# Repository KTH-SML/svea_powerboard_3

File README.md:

# Svea Powerboard Rev3

Repository structure:

- `firmware/` — Zephyr firmware workspace (intended root for app/boards/modules as this grows).
- `hardware/kicad/` — KiCad project root, symbols, footprints, models, datasheets, and manufacturing assets.
	- `hardware/kicad/*.kicad_sch` — all schematic sheets are flattened in the project root for simpler external-tool dependency resolution.
- `scripts/` — migration/cleanup/utility scripts and helper tooling.

Can be viewed on [Kicad viewer](https://kicanvas.org/?repo=https%3A%2F%2Fgithub.com%2FKTH-SML%2Fsvea_powerboard_3%2Ftree%2Fmain%2Fhardware%2Fkicad)
## Working folders

- Open KiCad project from `hardware/kicad/svea_powerboard_rev3.kicad_pro`.
- Run helper scripts from repo root, for example: `python scripts/rebuild_parent_hierarchy.py`.

## Notes

- Keep all generated/temporary KiCad artifacts out of version control via `.gitignore`.
- Keep firmware and hardware changes in separate commits when possible.

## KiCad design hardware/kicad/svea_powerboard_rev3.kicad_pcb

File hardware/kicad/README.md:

# I2C Rail Audit (`SCL_SLOW` / `SDA_SLOW`)

Generated on `2026-03-05` from:
- Schematic: `hardware/kicad/svea_powerboard_rev3.kicad_sch`
- Fresh netlist: `build/kicad/quality/netlist_i2c_audit.xml`

All addresses below are **7-bit I2C addresses unless explicitly noted otherwise**.

## Scope and method
1. Exported a fresh netlist with `kicad-cli sch export netlist`.
2. Enumerated every node on `SCL_SLOW` and `SDA_SLOW`.
3. Derived addresses from **actual pin straps + datasheet address tables**.
4. Did not trust symbol comments/labels as source of truth.

## Rail summary
| Rail | Pull-up | Net notes |
|---|---|---|
| `SCL_SLOW` | `R105 = 2.2k` to `+3V3` | Connected to all on-bus devices, `U83` connector pin 10, and `JP2001` pin 1 |
| `SDA_SLOW` | `R118 = 2.2k` to `+3V3` | Connected to all on-bus devices, `U83` connector pin 12, and `JP2002` pin 1 |

## I2C device matrix (address + speed)
| Ref | Device | Bus state on this board | Address (7-bit) | Supported I2C frequency (datasheet) | Strap / decode evidence |
|---|---|---|---|---|---|
| `CUR_1` | `INA3221AIRGVR` | Active on `SCL_SLOW/SDA_SLOW` | `0x40` | Fast + HS: up to `2.44 MHz` | `A0` via `R98` to `GND`; INA3221 address table (`A0=GND`) |
| `CUR_2` | `INA3221AIRGVR` | Active on `SCL_SLOW/SDA_SLOW` | `0x41` | Fast + HS: up to `2.44 MHz` | `A0` via `R162` to `+3V3`; INA3221 address table (`A0=VS`) |
| `U304` | `PCAL6524HEAZ` | Active on `SCL_SLOW/SDA_SLOW` | `0x23` | Fm+: up to `1 MHz` | `ADDR` via `R19` to `+3V3`; datasheet Table 4 gives `0x46/0x47` (8-bit) |
| `U3404` | `PCAL6524HEAZ` | Active on `SCL_SLOW/SDA_SLOW` | `0x22` | Fm+: up to `1 MHz` | `ADDR` via `R243` to `GND`; datasheet Table 4 gives `0x44/0x45` (8-bit) |
| `U44` | `MCP4725A0T-E/CH` | Active on `SCL_SLOW/SDA_SLOW` | `0x60` | Standard/Fast/HS: up to `3.4 MHz` | `A0` pin to `GND`; `A2/A1=00` option for A0 variant |
| `U601` | `TPL0401B-10DCKR` | Active on `SCL_SLOW/SDA_SLOW` | `0x3E` | Standard/Fast: up to `400 kHz` | TPL0401B bit address table (`0111110b`) |
| `U72` | `INA226AIDGSR` | Active on `SCL_SLOW/SDA_SLOW` | `0x4E` | Fast + HS: up to `2.94 MHz` | `A1=SCL`, `A0=SDA` |
| `U78` | `PCA9685PW,118` | Active on `SCL_SLOW/SDA_SLOW` | `0x61` | Fm+: up to `1 MHz` | `A5=1`, `A0=1` via `R186`, `A4..A1=0` via `R184,R183,R182,R181` |
| `U80` | `BQ7694202PFBR` | Active on `SCL_SLOW/SDA_SLOW` | `0x08` (default) | `100/400 kHz` | Datasheet default I2C target bytes `0x10/0x11` (8-bit) |
| `U81` | `INA226AIDGSR` | Active on `SCL_SLOW/SDA_SLOW` | `0x4F` | Fast + HS: up to `2.94 MHz` | `A1=SCL`, `A0=SCL` |
| `U1` | `LSM6DSOXTR` | Active on `SCL_SLOW/SDA_SLOW` | `0x6B` | Standard/Fast: up to `400 kHz` | `SA0` tied high (`SDO/SA0=+3V3`) |
| `U104` | `ADS1115IRUGT` | Active on `SCL_SLOW/SDA_SLOW` | `0x49` | Standard/Fast/HS: up to `3.4 MHz` | `ADDR=+3V3` |
| `U65` | `HUSB238A-BB001-QN16R` | **Isolated by default** (`JP2001`,`JP2002` open) | Conditional: datasheet notation is `62H` (`ADDR=VDD`) or `42H` (`ADDR=GND`); if those are 8-bit transfer bytes, equivalent 7-bit addresses are `0x31` / `0x21`; floating `ADDR` => GPIO mode (no I2C address) | Fast mode: up to `400 kHz` | `ADDR/ORIENT` is not hard-strapped to VDD/GND in this design: `U65.ADDR` -> `R2007` -> `USB-C/I2C/EN` -> `U302` -> `U304` |

`U83` is a direct bus connector endpoint (`SCL_SLOW/SDA_SLOW`) and can add external I2C devices/addresses.

## Findings that matter before ordering
1. No on-board 7-bit address collisions were found on `SCL_SLOW/SDA_SLOW` in this revision.
2. **PCAL6524 address format trap:** datasheet table is shown in 8-bit transfer form (`0x44/0x45`, `0x46/0x47`). Typical firmware APIs want 7-bit (`0x22`, `0x23`).
3. `U83` exposes the same rail externally, so any plugged module can still create address conflicts.
4. `U65` only has a valid I2C address if `ADDR/ORIENT` is forced high or low during initialization; if it is floating at init, the part enters GPIO mode.

## Same-bus compatibility check
1. **Clock-rate compatibility:** all active devices are compatible at `<= 400 kHz`; do not run this shared bus above `400 kHz` because `U601`, `U1`, and `U80` top out at fast/400 kHz.
2. **Mixed fast/HS parts are fine** as long as the controller keeps the bus at the common safe rate (`100 kHz` or `400 kHz`).
3. **Protocol behavior to account for in firmware:**
   - `U78` (`PCA9685`) has default All-Call behavior (address group behavior exists in addition to its normal target address).
   - `U104` (`ADS1115`) supports SMBus/general-call features.
   - `CUR_1/CUR_2/U72/U81` (`INA3221`/`INA226`) include SMBus-style timeout behavior.
   - `U80` (`BQ76942`) can require/expect settings such as speed/CRC mode depending on configuration.
4. **Pull-up / loading margin:** bus pull-ups are `2.2k` to `3.3V` (`~1.5 mA` sink current when line is LOW). This is generally fine for on-board population, but external modules on `U83` may add parallel pull-ups and increase sink-current/rise-time stress.
5. **If enabling `U65` onto this bus:** it is still frequency-compatible (`400 kHz` fast mode), but ensure `ADDR/ORIENT` is deterministically forced HIGH or LOW at init; floating means GPIO mode and no valid I2C target address.

## Recommended pre-order checks
1. Keep firmware-side addresses in 7-bit form (especially `PCAL6524` and `BQ76942`, where many docs show 8-bit transfer bytes).
2. If you plan to use the `U83` external connector, reserve/document external module addresses before assembly.

## Datasheet references used
All datasheets used for this audit are in `hardware/kicad/datasheets/`:
- `INA3221AIRGVR_TI.pdf`
- `INA226AIDGSR_TI.pdf`
- `ADS1115IDGST_TI.pdf`
- `PCAL6524DS_NXP.pdf`
- `PCA9685PW_118_NXP.pdf`
- `TPL0401B-10-Q1_TI.pdf`
- `BQ7694202PFBR_TI.pdf`
- `LSM6DSOX_C481766.pdf`
- `MCP4725A0T-E-CH_MICROCHIP.pdf`
- `HUSB238A-BB001-QN16R.pdf` (checked for the optional jumper-isolated path)

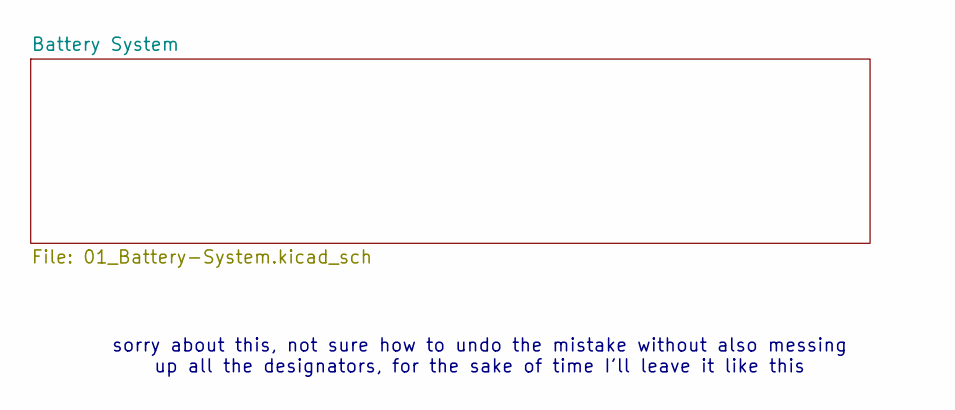
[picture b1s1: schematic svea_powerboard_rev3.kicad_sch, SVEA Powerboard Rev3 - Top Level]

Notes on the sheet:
sorry about this, not sure how to undo the mistake without also messing up all the designators, for the sake of time I'll leave it like this

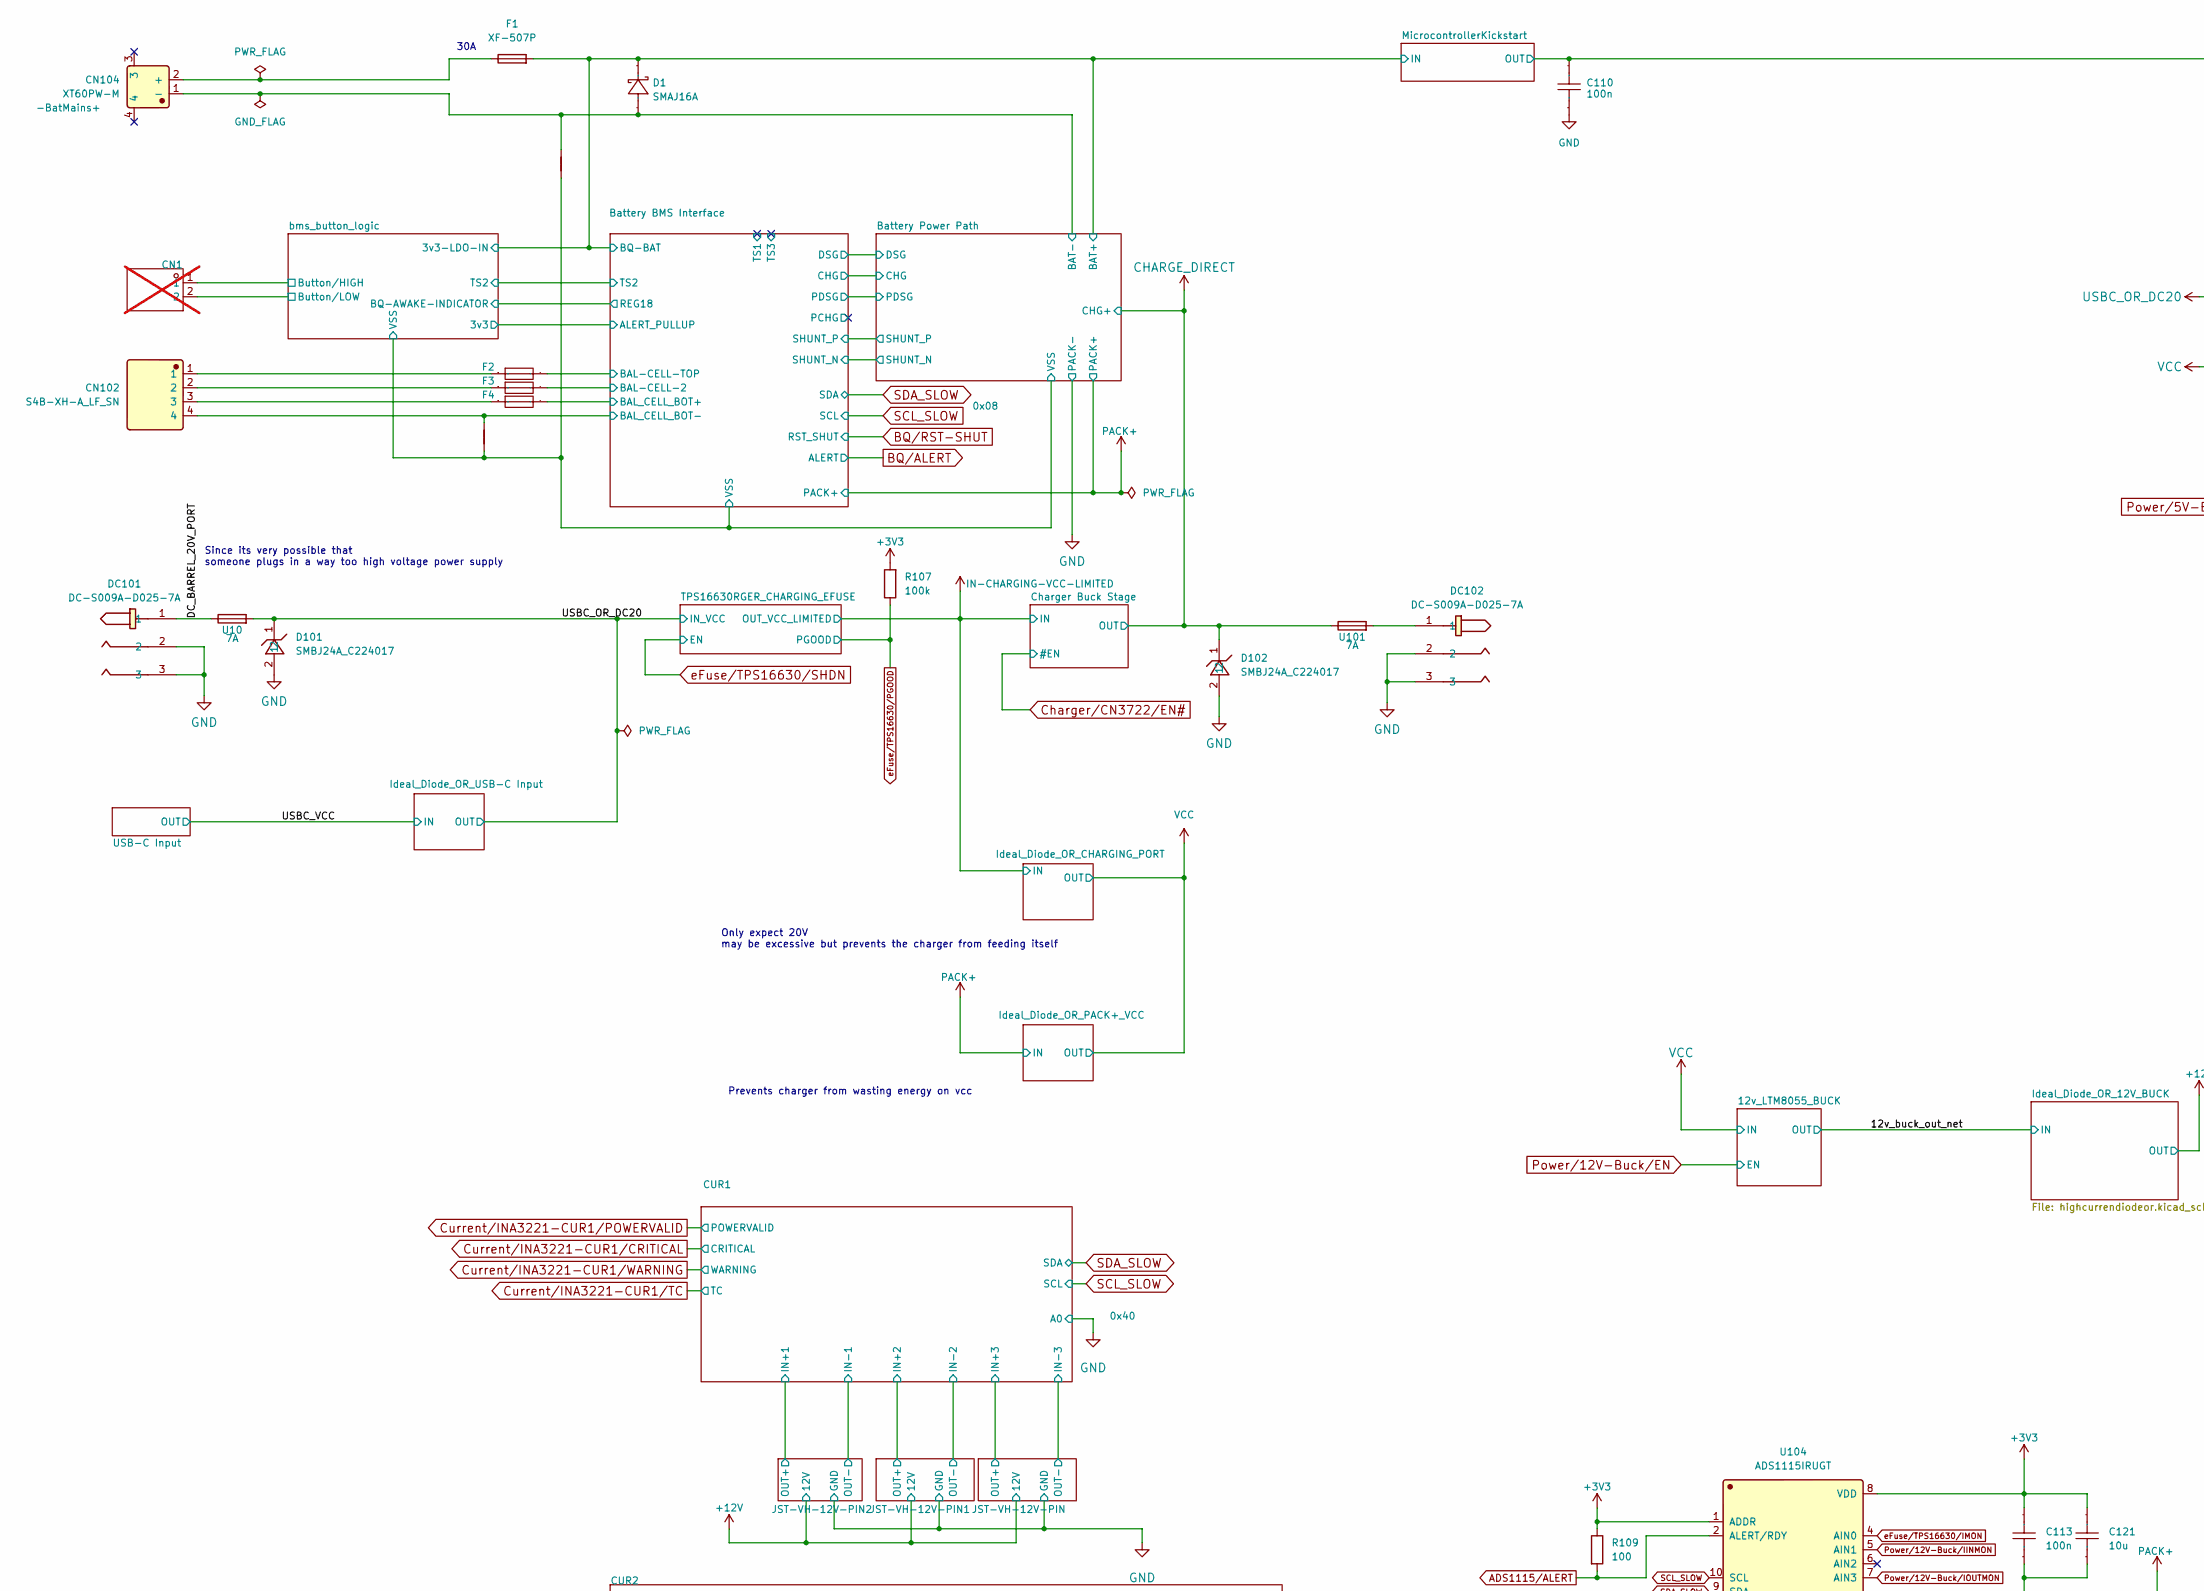
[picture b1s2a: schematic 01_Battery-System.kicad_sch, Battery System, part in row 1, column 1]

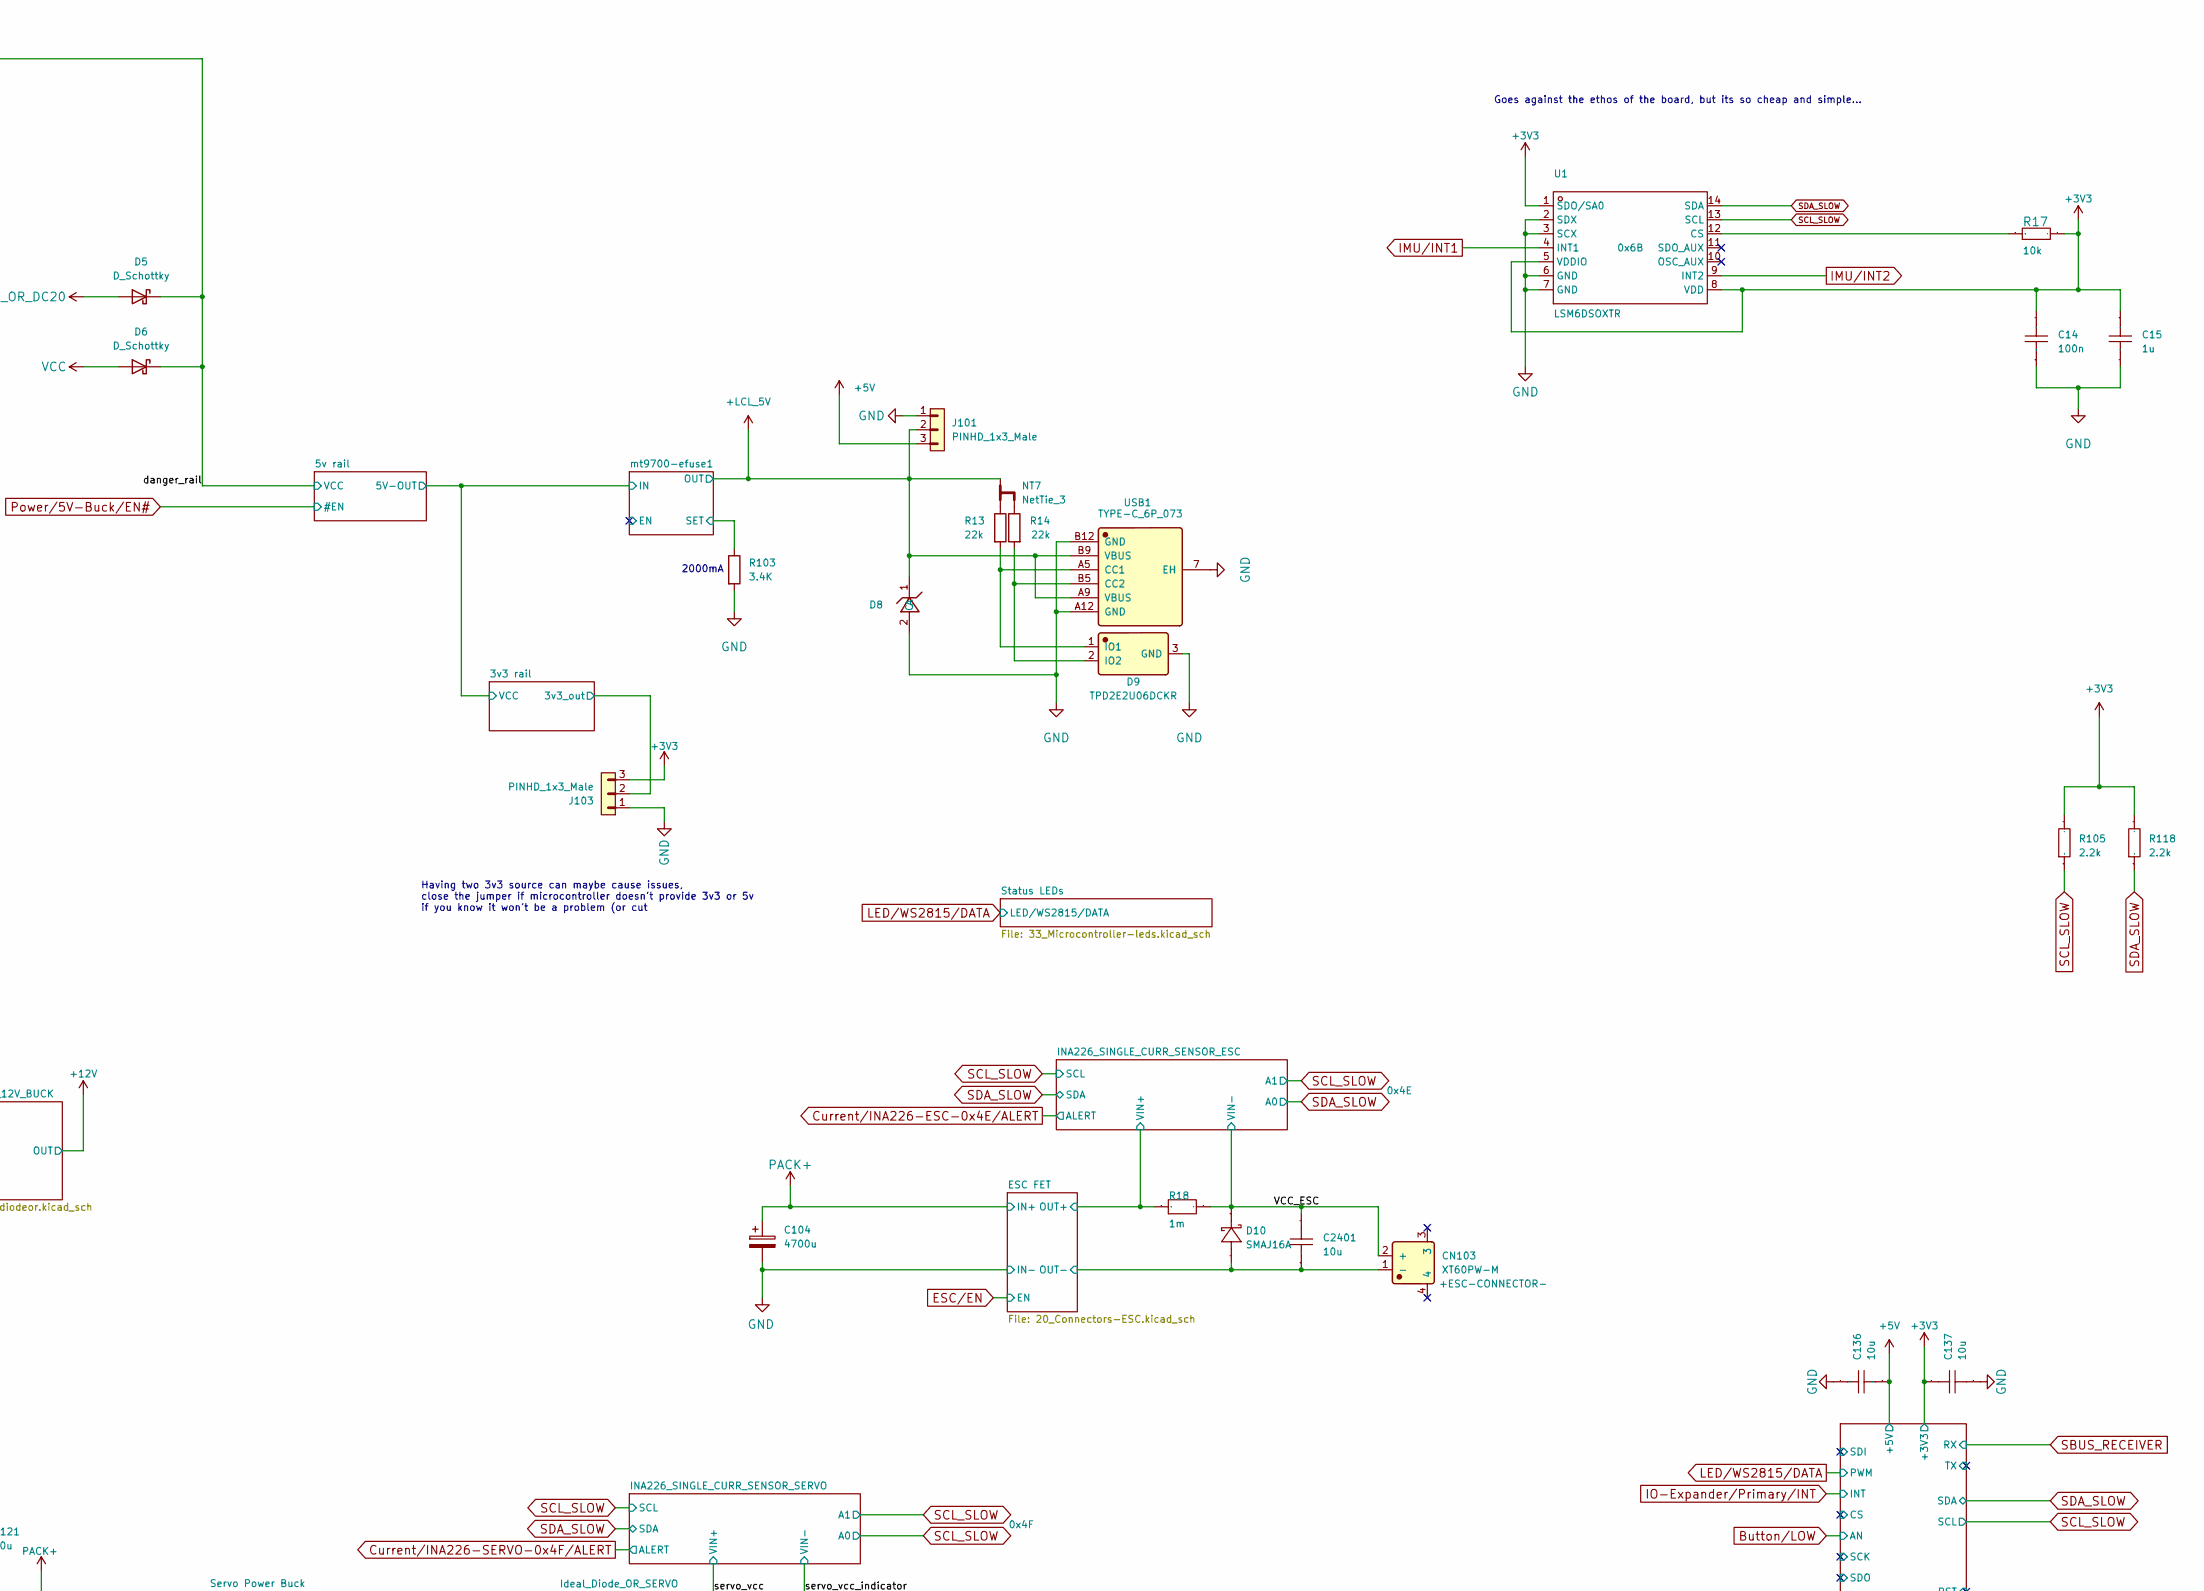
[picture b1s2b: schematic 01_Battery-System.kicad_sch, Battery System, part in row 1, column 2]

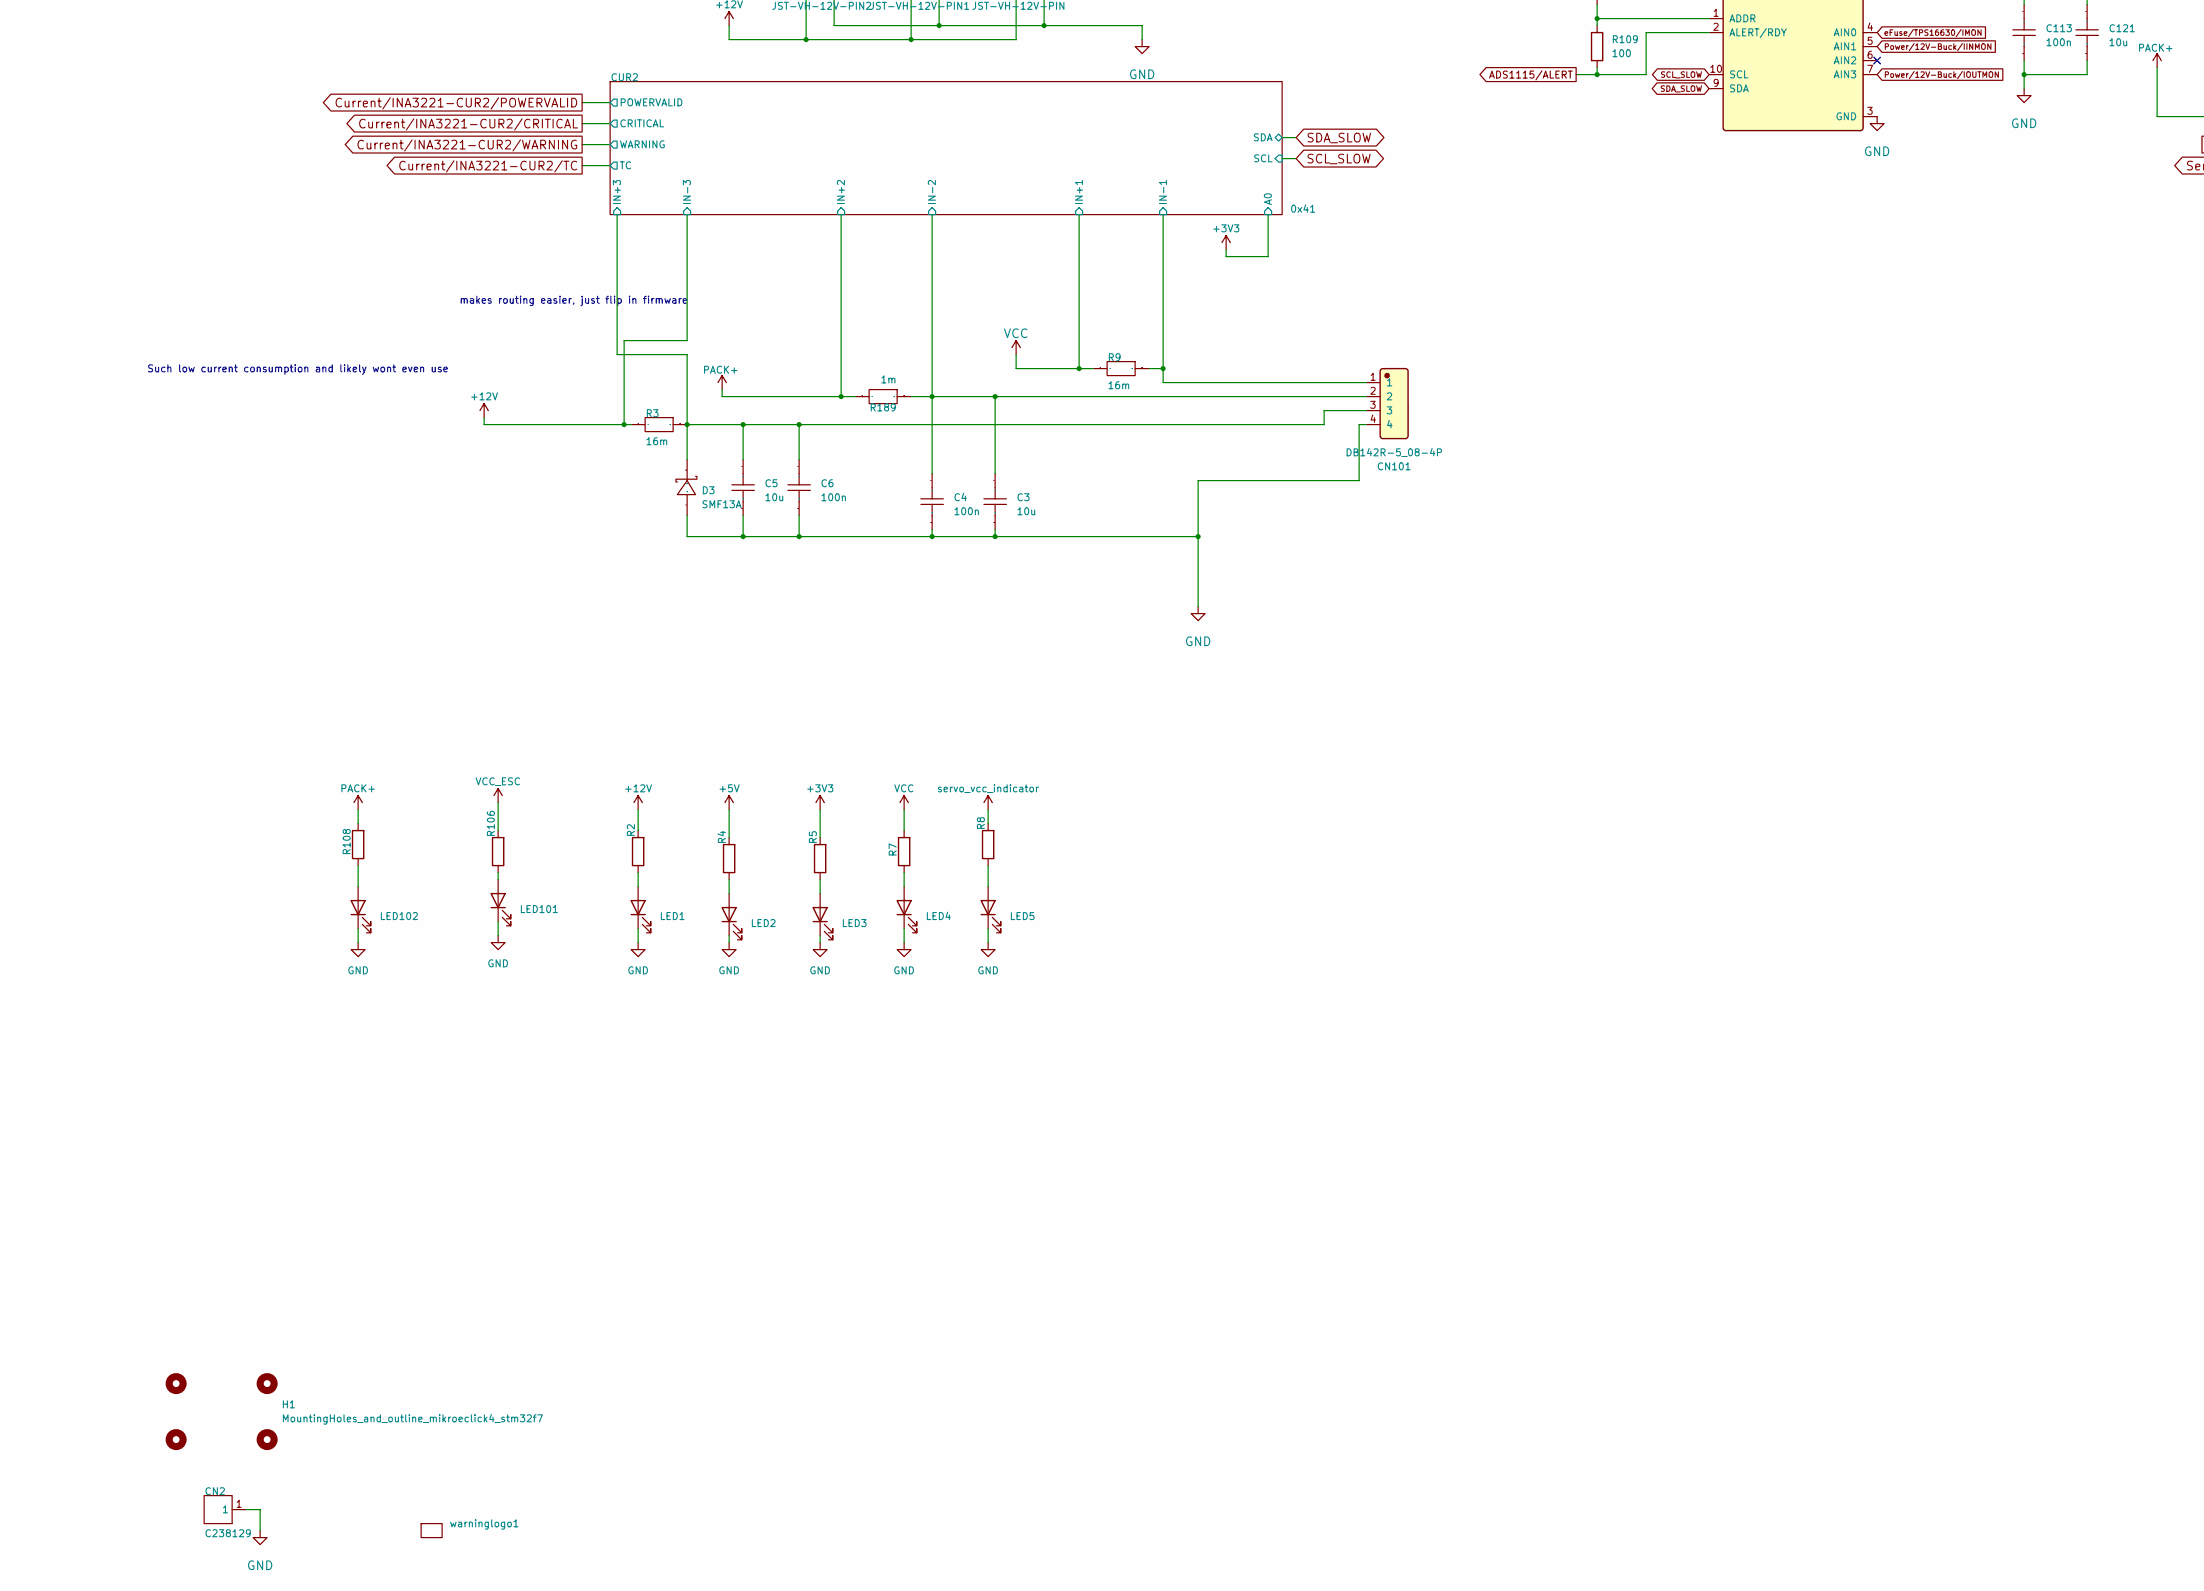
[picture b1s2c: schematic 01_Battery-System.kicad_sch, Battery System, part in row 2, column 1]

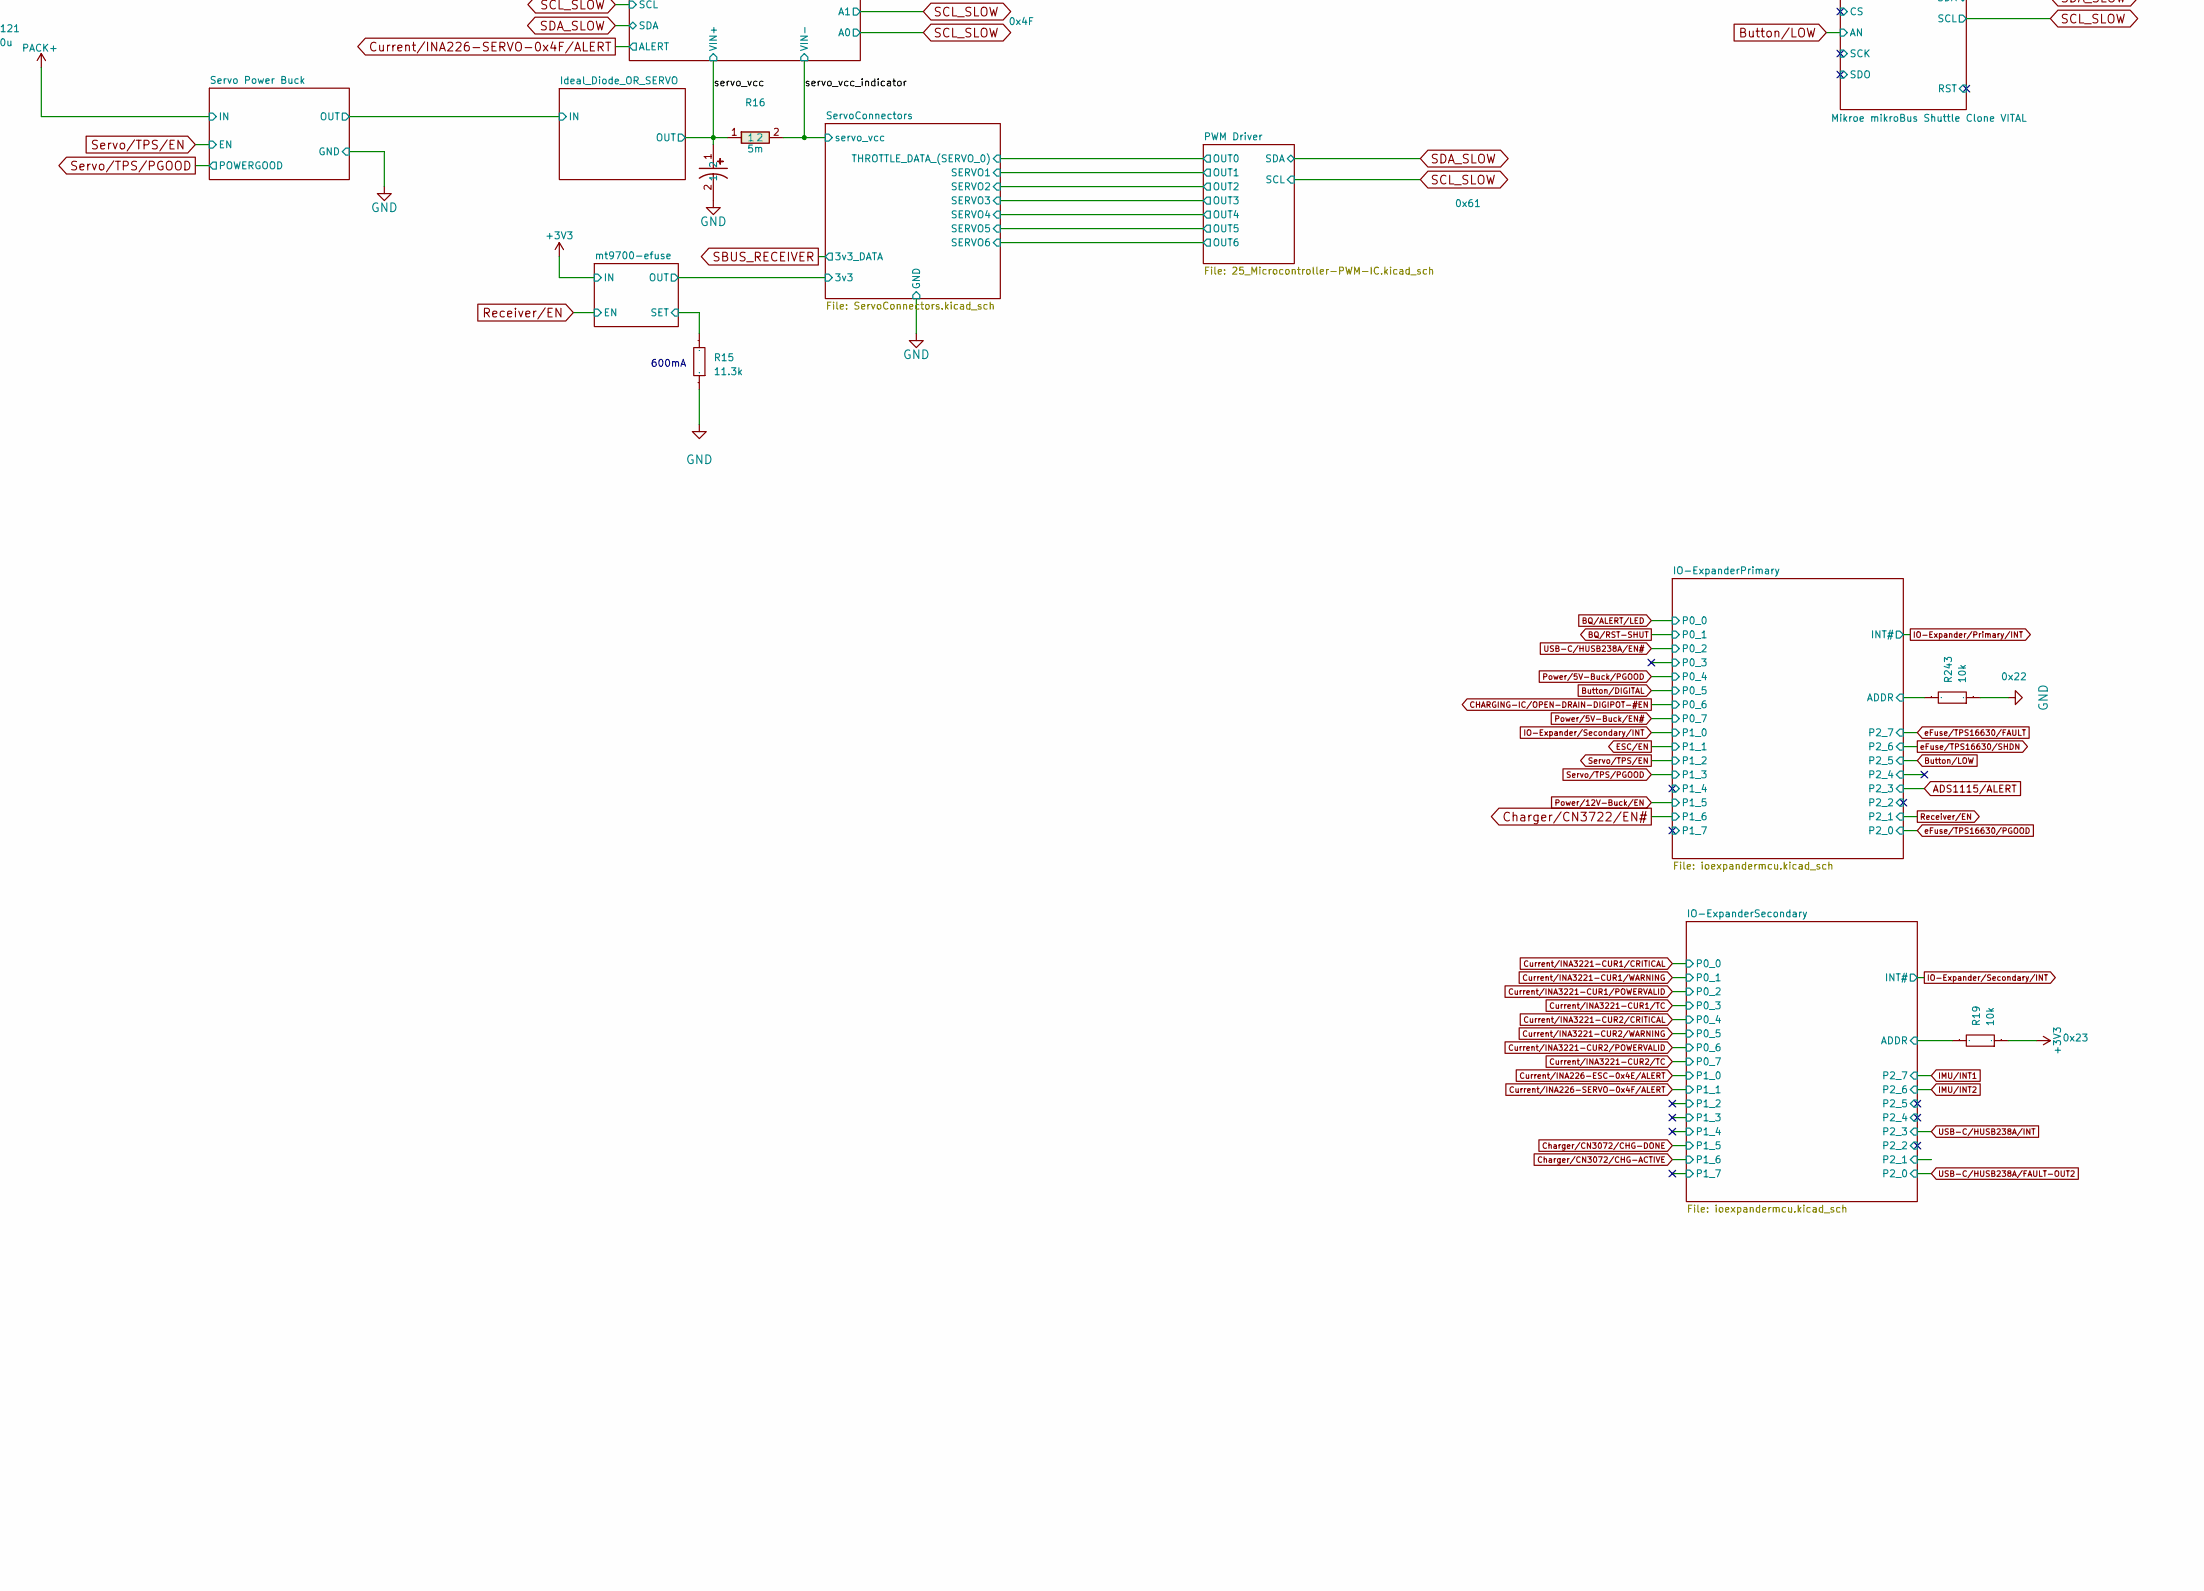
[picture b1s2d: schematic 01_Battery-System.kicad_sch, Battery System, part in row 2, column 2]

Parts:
C3, C5, C2401: 10u; C_0805_2012Metric; Manufacturer Part GRM21BR61H106KE43L; LCSC Part Name 10uF ±10% 50V
C4, C6, C14, C110, C113: 100n; C_0603_1608Metric; Manufacturer Part CC0603KRX7R9BB104; LCSC Part Name 100nF ±10% 50V
C15: 1u; C_0603_1608Metric; Manufacturer Part CL10B105KB8NQNC; LCSC Part Name 1uF ±10% 50V
C104: 4700u; 35PX4700MEFC16X35_5; lcsc C1600541
C121, C136, C137: 10u; C_0603_1608Metric; LCSC C237435
C143: VKME1651E102MV; Manufacturer Part VKME1651E102MV; LCSC C487334
CN1: B2B-XH-A(LF)(SN); CONN-TH_B2B-XH-A-LF-SN; Manufacturer Part B2B-XH-A(LF)(SN); LCSC Part Name 1x2P 间距:2.5mm 直插 系列:XH; not fitted
CN2: C238129; 5016; LCSC Part Name C238129
CN101: DB142R-5_08-4P; Manufacturer Part DB142R-5.08-4P-GN; LCSC C2898711
CN102: S4B-XH-A_LF_SN; Manufacturer Part S4B-XH-A(LF)(SN); LCSC C157925
CN103, CN104: XT60PW-M; Manufacturer Part XT60PW-M; LCSC C98732
D1, D10: SMAJ16A; D_SMA; Manufacturer Part SMAJ16A; LCSC Part Name 单向TVS 16V截止 15.3A峰值脉冲
D3: SMF13A; SOD-123F_L2.8-W1.8-LS3.7-RD; Manufacturer Part SMF13A; LCSC Part Name SMF13A
D5, D6: D_Schottky; D_SOD-123F; LCSC C719833
D8: SMF5_0A_C2857263; SOD-123F_L2.8-W1.8-LS3.7-RD; Manufacturer Part SMF5.0A; LCSC C2857263
D9: TPD2E2U06DCKR; SOT-323_SC-70; Manufacturer Part TPD2E2U06DCKR; LCSC C1855726
D101, D102: SMBJ24A_C224017; D_SMB; Manufacturer Part SMBJ24A; LCSC C224017
DC101, DC102: DC-S009A-D025-7A; Manufacturer Part DC-S009A-D025-7A; LCSC C7544903
F1: XF-507P; CONN-TH_XF-507P; LCSC C668119
F2, F3, F4: 0466001.NRHF; Fuse_1206_3216Metric; Manufacturer Part 0466001.NRHF; LCSC Part Name 63V贴片式保险丝
H1: MountingHoles_and_outline_mikroeclick4_stm32f7; stm32f7MikroeClick4Model
J101, J103: PINHD_1x3_Male; PinHeader_1x03_P2.54mm_Vertical; lcsc C42431836
LED1, LED2, LED3, LED4, LED5, LED101, LED102: XL-1608UBC-04; LED_0603_1608Metric; Manufacturer Part XL-1608UBC-04; LCSC C965807
NT1, NT2: NetTie_2; NetTie-2_SMD_Pad0.5mm
NT7: NetTie_3; NetTie-3_SMD_Pad0.5mm
R2, R106, R108: 4.7k; R_0603_1608Metric; Manufacturer Part 0603WAF4701T5E; LCSC C23162
R3, R9: 16m; R_2512_6332Metric; Manufacturer Part LR123WF160MT4E; LCSC Part Name 16mΩ ±1% 3W
R4, R8: 1k; R_0603_1608Metric; Manufacturer Part FRC0603F1001TS; LCSC C2907002
R5: 150; R_0603_1608Metric; Manufacturer Part 0603WAF1500T5E; LCSC C22808
R7: 4.02k; R_0603_1608Metric; Manufacturer Part 0603WAF4021T5E; LCSC C23040
R13, R14: 22k; R_0603_1608Metric; LCSC C31850
R15: 11.3k; R_0603_1608Metric; Manufacturer Part 0603WAF1132T5E; LCSC Part Name 11.3kΩ ±1% 100mW 厚膜电阻
R16: RLM25FEER005; Manufacturer Part RLM25FEER005; LCSC C185817
R17: 10k; R_0603_1608Metric; Manufacturer Part 0603WAF1002T5E; LCSC Part Name 厚膜电阻 10kΩ ±1% 100mW
R18, R189: 1m; R3920; Manufacturer Part PEWM3920F1L00K9; LCSC Part Name 1mΩ ±1% 8W
R19, R243: 10k; R_0402_1005Metric; Manufacturer Part 0402WGF1002TCE; LCSC Part Name 10kΩ ±1% 62.5mW 厚膜电阻
R103: 3.4K; R_0402_1005Metric; LCSC C4940
R105, R118: 2.2k; R_0603_1608Metric; LCSC C4190
R107: 100k; R_0402_1005Metric; LCSC C25741
R109: 100; R_0603_1608Metric; Manufacturer Part 0603WAF1000T5E; LCSC Part Name 100Ω ±1% 100mW 厚膜电阻
U1: LSM6DSOXTR; LGA-14L_L3.0-W2.5-P0.50-TL; Manufacturer Part LSM6DSOXTR; LCSC Part Name LSM6DSOXTR
U10, U101: 0440007_WR; Fuse_1206_3216Metric; Manufacturer Part 0440007.WR; LCSC C206973
U104: ADS1115IRUGT; Manufacturer Part ADS1115IRUGT; LCSC C701611
USB1: TYPE-C_6P_073; Manufacturer Part TYPE-C 6P(073); LCSC C668623
warninglogo1: triangle

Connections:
+3V3: C14.2, C15.1, C113.2, C121.2, C137.2, J103.3, R5.2, R17.2, R19.1, R105.2, R107.2, R109.1, R118.2, U1.1 (SDO/SA0), U1.5 (VDDIO), U1.8 (VDD), U104.1 (ADDR), U104.8 (VDD); also elsewhere on the board
+5V: C136.1, J101.3, R4.2; also elsewhere on the board
+12V: R2.2, R3.2; also elsewhere on the board
+LCL_5V: D8.1 (C), J101.2, NT7.2, USB1.A9 (VBUS), USB1.B9 (VBUS); also elsewhere on the board
/Battery System/3v3 rail/3v3_out: J103.2; also elsewhere on the board
/Battery System/Battery BMS Interface/BAL-CELL-2: F3.2; also elsewhere on the board
/Battery System/Battery BMS Interface/BAL-CELL-TOP: F2.2; also elsewhere on the board
/Battery System/Battery BMS Interface/BAL_CELL_BOT+: F4.2; also elsewhere on the board
/Battery System/Battery BMS Interface/BAL_CELL_BOT-: CN102.4, NT1.2; also elsewhere on the board
/Battery System/Battery BMS Interface/BQ-BAT: D1.1, F1.2; also elsewhere on the board
/Battery System/Battery BMS Interface/VSS: NT1.1, NT2.1; also elsewhere on the board
/Battery System/Battery Power Path/BAT-: CN104.1 (-), D1.2, NT2.2; also elsewhere on the board
/Battery System/CUR2/IN+3: C5.2, C6.2, CN101.3, D3.1 (K), R3.1; also elsewhere on the board
/Battery System/CUR2/IN-1: CN101.1, R9.1; also elsewhere on the board
/Battery System/CUR2/IN-2: C3.2, C4.2, CN101.2, R189.1; also elsewhere on the board
/Battery System/DC_BARREL_20V_PORT: DC101.1, U10.1
/Battery System/ESC FET/OUT+: R18.1; also elsewhere on the board
/Battery System/IO-ExpanderPrimary/ADDR: R243.2; also elsewhere on the board
/Battery System/IO-ExpanderSecondary/ADDR: R19.2; also elsewhere on the board
/Battery System/danger_rail: C110.2, D5.1 (K), D6.1 (K); also elsewhere on the board
/Battery System/mt9700-efuse1/SET: R103.1; also elsewhere on the board
/Battery System/mt9700-efuse/SET: R15.2; also elsewhere on the board
/Battery System/servo_vcc: C143.1, R16.1; also elsewhere on the board
ADS1115/ALERT: R109.2, U104.2 (ALERT/RDY); also elsewhere on the board
CHARGE_DIRECT: D102.1, U101.1; also elsewhere on the board
GND: C3.1, C4.1, C5.1, C6.1, C14.1, C15.2, C104.2, C110.1, C113.1, C121.1, C136.2, C137.1, C143.2, C2401.1, CN2.1 (1_1), CN101.4, CN103.1 (-), D3.2 (A), D8.2 (A), D9.3 (GND), D10.2, D101.2, D102.2, DC101.2, DC101.3, DC102.2, DC102.3, J101.1, J103.1, LED1.1 (K), LED2.1 (K), LED3.1 (K), LED4.1 (K), LED5.1 (K), LED101.1 (K), LED102.1 (K), R15.1, R103.2, R243.1, U1.2 (SDX), U1.3 (SCX), U1.6 (GND), U1.7 (GND), U104.3 (GND), USB1.7 (EH), USB1.A12 (GND), USB1.B12 (GND); also elsewhere on the board
IMU/INT1: U1.4 (INT1); also elsewhere on the board
IMU/INT2: U1.9 (INT2); also elsewhere on the board
unnamed: CN102.1, F2.1
unnamed: CN102.2, F3.1
unnamed: CN102.3, F4.1
unnamed: CN104.2 (+), F1.1
unnamed: D9.1 (IO1), R13.2, USB1.A5 (CC1)
unnamed: D9.2 (IO2), R14.2, USB1.B5 (CC2)
unnamed: DC102.1, U101.2
unnamed: LED1.2 (A), R2.1
unnamed: LED2.2 (A), R4.1
unnamed: LED3.2 (A), R5.1
unnamed: LED4.2 (A), R7.1
unnamed: LED5.2 (A), R8.1
unnamed: LED101.2 (A), R106.1
unnamed: LED102.2 (A), R108.1
unnamed: NT7.1, R13.1
unnamed: NT7.3, R14.1
unnamed: R17.1, U1.12 (CS)
PACK+: C104.1, R108.2, R189.2; also elsewhere on the board
SCL_SLOW: R105.1, U1.13 (SCL), U104.10 (SCL); also elsewhere on the board
SDA_SLOW: R118.1, U1.14 (SDA), U104.9 (SDA); also elsewhere on the board
USBC_OR_DC20: D5.2 (A), D101.1, U10.2; also elsewhere on the board
VCC: D6.2 (A), R7.2, R9.2; also elsewhere on the board
VCC_ESC: C2401.2, CN103.2 (+), D10.1, R18.2, R106.2; also elsewhere on the board
eFuse/TPS16630/IMON: U104.4 (AIN0); also elsewhere on the board
eFuse/TPS16630/PGOOD: R107.1; also elsewhere on the board
servo_vcc_indicator: R8.2, R16.2; also elsewhere on the board

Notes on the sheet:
makes routing easier, just flip in firmware
Only expect 20V may be excessive but prevents the charger from feeding itself
Having two 3v3 source can maybe cause issues, close the jumper if microcontroller doesn't provide 3v3 or 5v if you know it won't be a problem (or cut
2000mA
30A
Since its very possible that someone plugs in a way too high voltage power supply
600mA
Goes against the ethos of the board, but its so cheap and simple...
Such low current consumption and likely wont even use
Prevents charger from wasting energy on vcc
